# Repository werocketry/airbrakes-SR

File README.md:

# airbrakes-SR

This is the repository for the Western Engineering Rocketry Team's design of an airbrakes system.

## Sister Projects

- [werocketry/RocketFlightSim](https://github.com/werocketry/RocketFlightSim)
- [werocketry/HPR-Rocket-Flight-Computer](https://github.com/werocketry/HPR-Rocket-Flight-Computer)

## Acronyms of the Trade
| Acronym | Full Name                                 | Description                                                                          |
|---------|-------------------------------------------|--------------------------------------------------------------------------------------|
| AGL     | Above Ground Level                        |                                                                                      |
| COTS    | Commercial off-the-shelf                  |                                                                                      |
| CP      | Center of pressure                        |                                                                                      |
| ESRA    | Experimental Sounding Rocket Association  |                                                                                      |
| FOS     | Factor of Safety                          |                                                                                      |
| FS      | Factor of Safety                          |                                                                                      |
| IREC    | Intercollegiate Rocket Engineering Competition | Basically SAC. It used to happen somewhere else                                       |
| NM      | New Mexico                                |                                                                                      |
| NMSU    | New Mexico State University               | The university on whose grounds some parts of SAC are held                           |
| OR      | OpenRocket                                |                                                                                      |
| .ork    | OpenRocket filetype                       |                                                                                      |
| RSO     | Range Safety Officer                      | The person that gives you permission to launch                                       |
| SA      | Spaceport America                         | The launch site where SAC is hosted                                                  |
| SAC     | Spaceport America Cup                     |                                                                                      |
| SRAD    | Student researched and designed           |                                                                                      |
| VLA     | Vertical Launch Area                      |                                                                                      |
| WERT    | Western Engineering Rocketry Team         | Also called WE Rocketry                                                              |

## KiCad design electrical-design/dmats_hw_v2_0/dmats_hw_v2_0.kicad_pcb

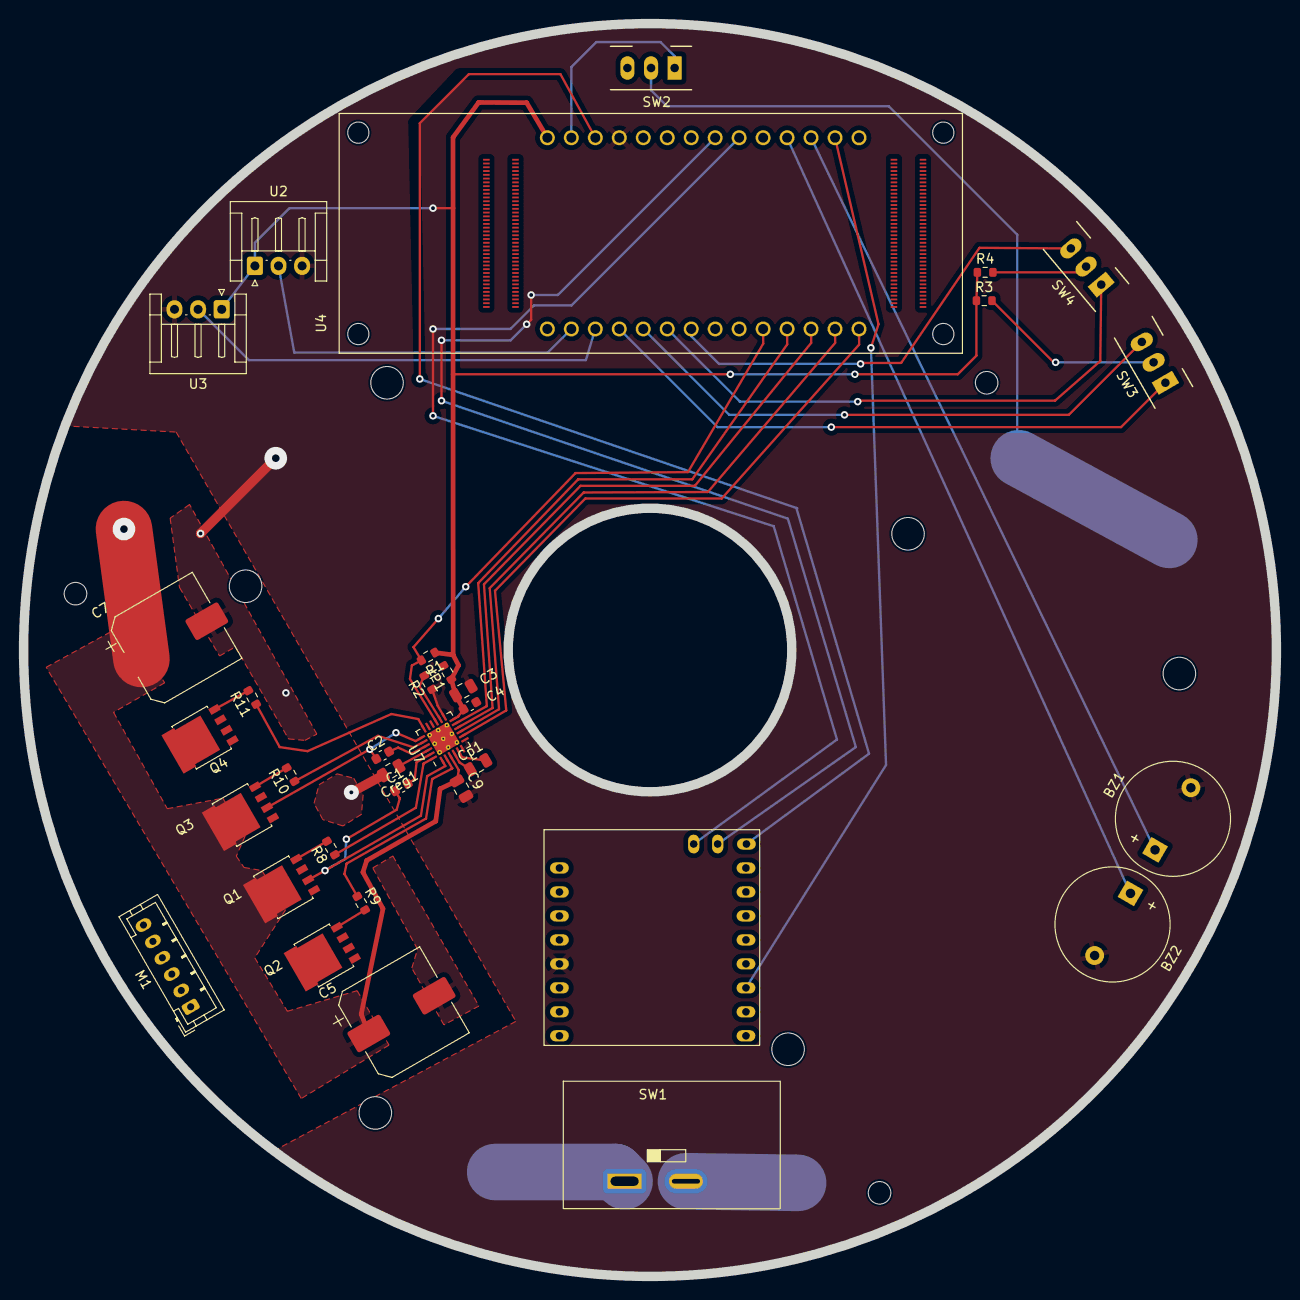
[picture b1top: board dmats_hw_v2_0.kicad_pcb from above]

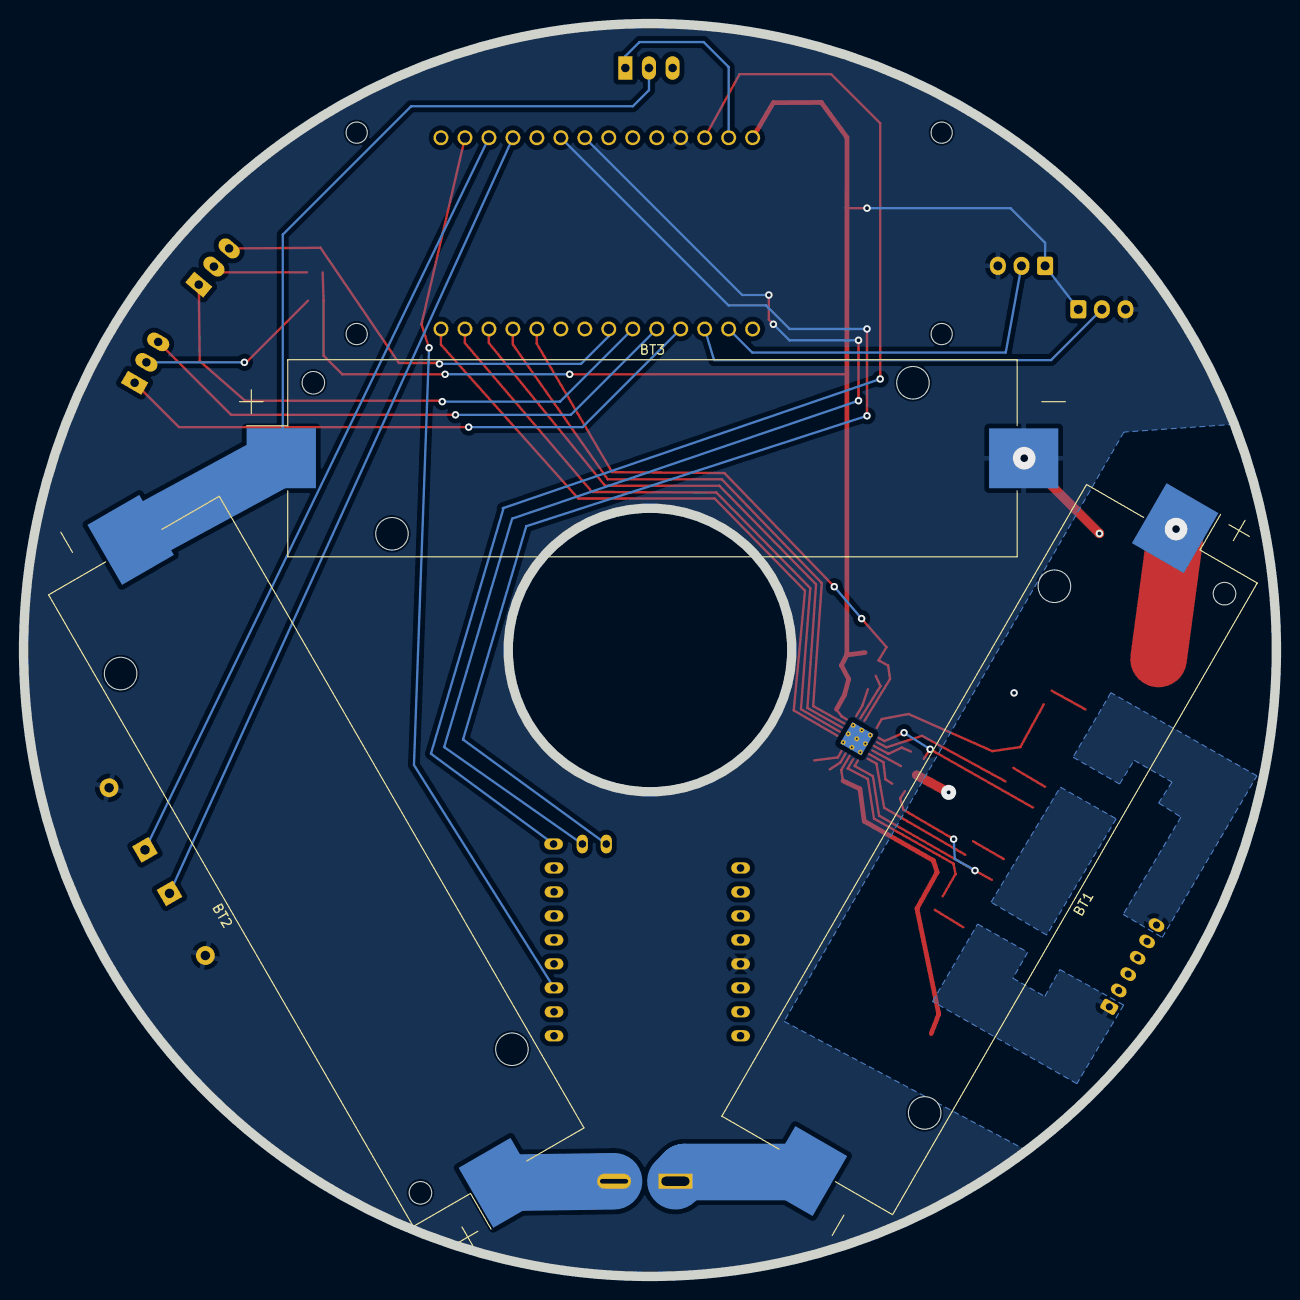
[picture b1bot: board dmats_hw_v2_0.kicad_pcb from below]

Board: 2 copper layers, 132.7 x 132.7 mm, 37 parts (3 on the bottom side), 47 nets.

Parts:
BT1, BT2, BT3: 3V7 LI-ION; BatteryHolder_Keystone_1042_1x18650
BZ1, BZ2: Buzzer; Buzzer_12x9.5RM7.6
C1, C2: 10n; C_0603_1608Metric
C3: 10U; C_0805_2012Metric
C4: 100N; C_0603_1608Metric
C5, C7: 50V 220U; CP_Elec_10x10
C9: 50V 10U; C_0805_2012Metric
Cp1: 16V 470n; C_0805_2012Metric
Creg1: 16V 22u; C_0805_2012Metric
JP1: Jumper_2_Open; R_0603_1608Metric
M1: Motor_2BitEncoder; JST_PH_B6B-PH-K_1x06_P2.00mm_Vertical
Q1, Q2, Q3, Q4: PSMN1R0-30YLC,115; LFPAK56
R1, R2: 10K; R_0603_1608Metric
R3, R4: 10k; R_0603_1608Metric
R8, R9, R10, R11: 1K; R_0603_1608Metric
SW1: SW_SPST; SW_DIP_SPSTx01_Slide_Power
SW2, SW3, SW4: SW_SPDT; CUI_SLW-913535-2A-RA-D_SPDT_Angled
U1: ARDUINO_NICLA
U2, U3: A1324; JST_EH_S3B-EH_1x03_P2.50mm_Horizontal
U4: ABX00042; MODULE_ABX00042
U7: HVQFN-24-1EP_4x4mm_P0.5mm_EP2.6x2.6mm_ThermalVias

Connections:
+3.3V: U1.9 (VBAT), U4.JD3 (+3V3)
+5V: C3.1, C4.1, JP1.1 (A), M1.2 (VCC), R1.1, R3.1, R4.1, U2.1 (VCC), U3.1 (VCC), U4.JD1 (+5V), U7.12 (VDD)
+BATT: BT1.1 (+), C5.1, C7.1, C9.1, Q1.5 (D), Q3.5 (D), U7.3 (VBB)
/A4957_driver/GHA: R8.1, U7.24 (GHA)
/A4957_driver/GHB: R10.1, U7.20 (GHB)
/A4957_driver/GLA: R9.1, U7.2 (GLA)
/A4957_driver/GLB: R11.1, U7.18 (GLB)
/A4957_driver/RDEAD: JP1.2 (B), R2.2, U7.14 (RDEAD)
/AHI: U4.JA11 (D2), U7.11 (AHI)
/ALO: U4.JA12 (D3), U7.10 (ALO)
/BHI: U4.JA13 (D4), U7.9 (BHI)
/BLO: U4.JA14 (D5), U7.8 (BLO)
/BZ_A: BZ1.1 (-), U4.JD12 (D8)
/BZ_B: BZ2.1 (-), U4.JD11 (D9)
/FAULT: R1.2, U4.JA10 (D1), U7.15 (FAULT)
/GPIO_CS: U1.3 (6/CS), U4.JD13 (D7)
/HES_OUT1: U2.2 (VOUT), U4.JA2 (A0_D15)
/HES_OUT2: U3.2 (VOUT), U4.JA3 (A1_D16)
/I2C-SCL: U1.18 (3/SCL1), U4.JD8 (D12)
/I2C-SDA: U1.19 (4/SDA1), U4.JD9 (D11)
/M1: C1.1, M1.1 (M1), Q1.1 (S), Q1.2 (S), Q1.3 (S), Q2.5 (D), U7.1 (SA)
/M2: C2.1, M1.6 (M2), Q3.1 (S), Q3.2 (S), Q3.3 (S), Q4.5 (D), U7.19 (SB)
/SW_A: SW3.1 (A), U4.JA4 (A2_D17)
/SW_B: SW3.3 (C), U4.JA5 (A3_D18)
/SW_C: SW4.1 (A), U4.JA6 (A4_D19)
/SW_D: SW4.3 (C), U4.JA7 (A5_D20)
/VIN: SW2.1 (A), U4.JD2 (VIN_1)
GND: BT3.2 (-), BZ1.2 (+), BZ2.2 (+), C3.2, C4.2, C5.2, C7.2, C9.2, Creg1.2, M1.5 (GND), Q2.1 (S), Q2.2 (S), Q2.3 (S), Q4.1 (S), Q4.2 (S), Q4.3 (S), R2.1, U1.14 (GND), U2.3 (GND), U3.3 (GND), U4.JD4 (GND_2), U7.6 (GND), U7.7 (GND), U7.13 (AGND), U7.17 (GND)
unnamed: BT1.2 (-), SW1.1 (A)
unnamed: BT2.1 (+), SW1.2 (B)
unnamed: BT2.2 (-), BT3.1 (+), SW2.2 (B)
unnamed: Q1.4 (G), R8.2
unnamed: Q2.4 (G), R9.2
unnamed: Q3.4 (G), R10.2
unnamed: Q4.4 (G), R11.2
unnamed: R3.2, SW3.2 (B)
unnamed: R4.2, SW4.2 (B)
unnamed: U4.J1_22 (GND), U4.J1_31 (GND), U4.J1_42 (GND), U4.J1_47 (GND), U4.J1_54 (GND)
unnamed: U4.J1_21 (VIN), U4.J1_32 (VIN), U4.J1_41 (VIN), U4.J1_48 (VIN)
unnamed: U4.J1_53 (VSYS), U4.J1_64 (VSYS)
unnamed: U4.J2_24 (GND_1), U4.J2_33 (GND_1), U4.J2_44 (GND_1), U4.J2_57 (GND_1), U4.J2_70 (GND_1)
unnamed: U4.J2_23 (VCC/+3V3), U4.J2_43 (VCC/+3V3), U4.J2_69 (VCC/+3V3)
unnamed: C1.2, U7.23 (CA)
unnamed: C2.2, U7.21 (CB)
unnamed: Cp1.2, U7.5 (CP1)
unnamed: Cp1.1, U7.4 (CP2)
unnamed: Creg1.1, U7.22 (VREG)

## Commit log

2023-10-13 modified: README.md
2023-10-13 modified: data_manip.ipynb
2023-10-16 Added flaps taking time to deploy to PID simulation
2023-10-16 Minor parameter adjustments
2023-10-16 Added drag to custom flight profile during ascent
2023-10-16 Controller now outputs max deployment angle after target apogee
2023-10-17 optimizations, minor enhancements
2023-10-17 New folder for prelim flight analysis
2023-10-17 Rename data_manip.ipynb to preliminary_flight_analysis/data_manip.ipynb
2023-10-17 Rename README.md to preliminary_flight_analysis/README.md
2023-10-18 added sensor / board documentation & design files
2023-10-20 changed airbrake parameters
2023-10-20 minor changes
2023-10-20 rearrange
2023-10-21 save time
2023-11-05 parameter updates, notebook shows more data
2023-11-10 Provide more information, update parameters, make better use of telemega and telemetrum datasets
2023-11-10 cleaned up, easier to set up custom sims
2023-11-10 misc updates
2023-11-11 Towards a dynamic Cd_rocket
2023-11-12 Improved simulation, more detailed analysis
2023-11-13 minor
2023-11-13 q in final graphs instead of speed
2023-11-14 improved flight simulation
2023-11-14 more accurate sim
2023-11-15 added tutorial to get started on windows
2023-11-20 minor update
2023-11-20 add Prometheus ORK file
2023-11-21 checkpoint save
2023-11-22 refactored simulation into seperate file added consideration for launch angle off the vertical in sim various minor updates
2023-11-23 minor cleanup
2023-11-27 moved running ideas list into repo
2023-12-02 first sim of Hyperion
2023-12-05 added electrical schematic start and resources
2023-12-06 rename data_manip
2024-01-03 fixed visualizations calling of ascent simulation with airbrakes to use the proper rocket parameters (not always Prometheus')
2024-01-03 down to 3 flaps
2024-01-10 Cleanup
2024-01-11 Cross-sectional area now includes fins
2024-01-11 rename sim folder
2024-01-12 Misc improvements, cleanup
2024-01-14 launch angle now 10 deg off vertical updated airbrakes flap size
2024-01-15 launch rail length now accounts for added DOFs when only one launch lug left on rail (almost negligeable change ~10ft)
2024-01-15 created separate configs.py file to hold sets of parameters used to make instances of the custom classes
2024-01-16 added electrical sketch for controls
2024-01-18 did some refactoring of sims and repo structure
2024-01-18 refactored the flight sim file strcuture, added load analysis template
2024-01-18 minor formatting
2024-01-18 minor performance improvement
2024-01-18 Added STEP Files
2024-01-19 organized rest of functions including visualization
2024-01-19 Added Assemblies at different Angles
2024-01-19 minor wording changes
2024-01-19 load analysis outline complete - statics needs review
2024-01-19 added images and sources to load analysis
2024-01-19 load analysis statics fix
2024-01-19 load analysis updated
2024-01-20 updated analyses, an attempt at trying out servo and updated sims
2024-01-20 updated analyses, an attempt at trying out stepper and updated sims
2024-01-23 - Initial sensitivity analysis - Updated Hyperion's length - Fixed improper calling of simulate_airbrakes_flight in visualizations notebook
2024-01-23 small analyses of sensitivity analysis
2024-01-24 Updated Hyperion dry mass
2024-01-26 renamed "launch lug" to "rail button" (because that's what they are)
2024-01-28 prep for updatable configs
2024-02-04 - updated Hyperion mass - updated sensitivity analysis
2024-02-09 updated pressures and temperatures used in sensitivity analysis
2024-02-10 added stopping power analysis
2024-02-11 added battery design work
2024-02-12 - option for variations in sensitivity analysis to be drawn from a gaussian instead of just a linspace - added wind correction (flat -300 ft) to stopping power sim
2024-02-13 began integration of aero simulations and load analysis
2024-02-16 optimizations to sim: - default timestep of simulation (with and without airbrakes) now 0.01 instead of 0.001 (they only differ by about 2m in apogee) - brought conversion to radians of parameters de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
2024-02-17 Small simulation efficieny improvement. Got rid of previous_height variable. Final loops now end at v_y <=0
2024-02-20 - cleaned up - fixed TeleMega data in visualizations_cleaned
2024-02-21 - added RocketPy sim - refactored classes, now have motor class
2024-02-21 - added Prometheus RocketPy sim - some organization
2024-02-22 added airbrakes to RocketPy sim
2024-02-27 added some more stuff for motor analysis
2024-03-05 added some parts for data collection
2024-03-05 start of sim that might be put on the controller
2024-03-06 updated rocket mass and engine dry mass
2024-03-06 ran rocketpy sim with new masses, updated notebook
2024-03-10 added electrical schematic
2024-03-11 - updated airbrake parameters - minor other changes
2024-03-12 updated onboard flight sim
2024-03-12 added software libs
2024-03-12 - fixed outdated static call of flap area in load analysis within flight-simulator directory - cleanup -added ideas, TODOs to track what still needs doing - various minor changes
2024-03-14 Added a more precise temperature lapse rate
2024-03-17 updates to ece
2024-03-18 motor servo software updates
2024-03-20 - updated rocket mass - added a little to controller flight simulator - minor edits
2024-03-20 added altitude estimator test
2024-03-20 ported std devs script and got 2/3 working
2024-03-21 - updated airbrakes flap area, rocket fin thickness, rocket mass - updates to RocketPy parameters
2024-03-22 software controls changes
2024-03-26 added some Cd curves from ork
2024-03-28 Fixed Cd from Re in RocketPy sim
2024-03-29 changed default sim timestep, other minor tweaks
2024-03-30 begin implementing lookup tables
2024-03-31 ability to determine deployment angles for lookup tables
2024-03-31 more granular and efficient generation of deployment angle lookups
2024-03-31 made first lookup table
2024-03-31 changed lookup table location
2024-03-31 changed lookup table directory to flight-simulator
2024-04-02 software tweaks and development of A4957 custom driver
2024-04-02 v2 of circuit for PCB
2024-04-02 removed old log file
2024-04-03 created all PCB footprints
2024-04-04 bulk of PCB design layout complete
2024-04-04 PCB work
2024-04-05 completed motor driver PCB
2024-04-06 software dir refactoring before flight computer merge
2024-04-08 rewrote sim, classes, and other scripts to take Cd as a function of Ma instead of Re
2024-04-09 sim updates for force analysis and visual clean up on elec drawings
2024-04-09 added max theoretical calcs for g-force and q, other minor changes
2024-04-09 Initial commit splitting capstone repo
2024-04-20 transfer and beef up of documentation
2024-04-20 Configure LFS to track SolidWorks, STEP, and STL files
2024-04-20 Update README.md with sister project links
2024-04-21 minor documentation updates
2024-04-22 moved controller flight simulator, this year's configs, and lookup table generator to airbrakes repo from flight sim repo
2024-04-23 added note about rocket characteristics to wind tunnel test plan
2024-04-24 changed some notes about future work in two files
2024-04-24 added a few things from Teams, minor fixes to docs
2024-05-08 updated launch conditions for RFS' new generalized local gravity and temp lapse rate
2024-05-09 updated Hyperion values
2024-05-11 specify launch conditions for sim
2024-05-13 rocketpy sims updates
2024-05-14 updated RocketPy sims
2024-05-15 Prometheus RocketPy fins adjusted
2024-05-16 fix for visualizing Prometheus flight data
2024-05-16 updated visualizations to new Hyperion parameters, fixed bug when plotting aerodynamics in metric
2024-05-22 updated to use rocketflightsim as a package
2024-05-23 Added minor note about possible future use of Prometheus data in airbrakes simulations
2024-05-26 updated sims with newest mass budget
2024-05-27 updated sims with newest mass budget, newest updates to RFS
2024-05-29 updated configs, simulations with newest mass updates
2024-05-31 update sims with newest version of RFS
2024-06-02 updated sims with new launch angle
2024-06-08 updates of configs with new masses, updates of sims, start of new advanced lookup table generation
2024-06-11 updated sims with new drag curve
2024-06-13 added minor note to self
2024-06-18 cleaned configs for comp
2024-06-18 Tuesday morning updates to configs, sensitivity analysis
2024-06-22 final updates from competition
2024-07-05 addition of Hyperion flight data
